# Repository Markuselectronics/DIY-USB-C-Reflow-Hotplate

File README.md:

# 🔥 DIY USB-C PD Reflow Hotplate

**A professional, pocket-sized soldering hotplate powered by USB-C Power Delivery.**

This repository contains all design files for the project.
👉 **Full Tutorial & Guide:** [Link to your Instructables Page]

## 📂 Repository Structure

* **`/Manufacturing`**: Gerber files for JLCPCB.
  * `HotPlate.zip` (Use SMT Assembly)
  * `Plate` (**Order as Aluminum PCB!**)
* **`/Firmware`**: Source code for the STM32 microcontroller.

## ⚠️ Warning
**Hot Surface!** This device reaches 250°C+. Use with caution.

## 🤝 Credits
Huge thanks to **JLCPCB** for sponsoring the PCBs for this project.

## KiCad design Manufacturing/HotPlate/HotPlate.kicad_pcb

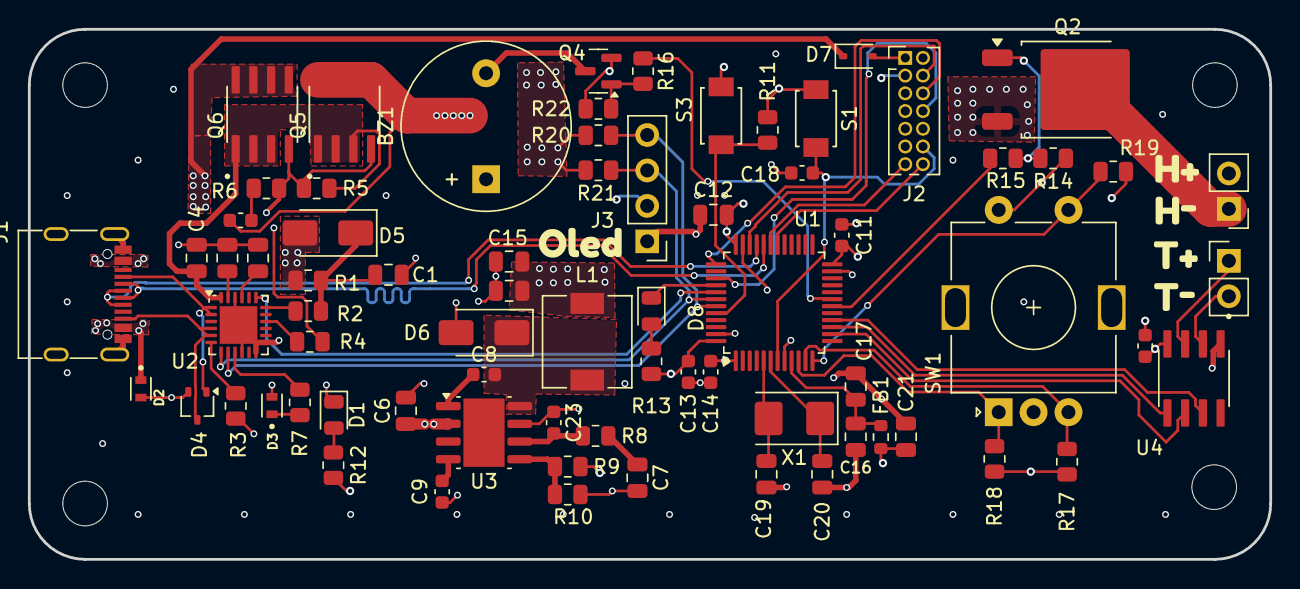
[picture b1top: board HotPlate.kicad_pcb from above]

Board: 4 copper layers, 89.0 x 38.0 mm, 82 parts (0 on the bottom side), 56 nets.

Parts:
BZ1: Buzzer; Buzzer_12x9.5RM7.6
C1, C2, C3, C4, C17, C21: 1uF; C_0805_2012Metric
C5, C8, C11, C13, C14, C18, C22: 100nF; C_0603_1608Metric
C6, C12: 10uF; C_0805_2012Metric
C7: 6n8; C_0805_2012Metric
C9: 8n2; C_0603_1608Metric
C10, C15: 47uF; C_0805_2012Metric
C16: 10nF; C_0805_2012Metric
C19, C20: 20pF; C_0805_2012Metric
C23: 10pF; C_0603_1608Metric
D1: green; D_0805_2012Metric
D2, D3: ESDA25P35-1U1M; TVS_ESDA25P35-1U1M
D4: ESDA25W; SOT-323_SC-70
D5, D6: SS14; D_SMA
D7: 1N5819WS; D_SOD-323
D8: yellow; D_0805_2012Metric
FB1: 120R; R_0603_1608Metric
H1, H2, H3, H4: MountingHole; MountingHole_3.2mm_M3
J1: USB-C; SHOU HAN TYPE-C 16PIN 2MD(073)
J2: Conn_ST_STDC14; PinHeader_2x07_P1.27mm_Vertical
J3: OLED-Display; PinHeader_1x04_P2.54mm_Vertical
J4: Thermocouple; PinHeader_1x02_P2.54mm_Vertical
J5: Heating Element; PinHeader_1x02_P2.54mm_Vertical
L1: 18uH; L_6.3x6.3_H3
Q2: MDD50N03D; TO-252-2
Q4: SS8050; SOT-23
Q5, Q6: AO4485; SOIC127P600X175-8N
R1: 470R; R_0805_2012Metric
R2: 1k; R_0805_2012Metric
R3, R9, R11, R14, R17, R18, R19, R22: 10k; R_0805_2012Metric
R4: 22k; R_0805_2012Metric
R5, R7: 100k; R_0805_2012Metric
R6: 100R; R_0805_2012Metric
R8: 4k99; R_0805_2012Metric
R10: 3k3; R_0805_2012Metric
R12, R13, R20, R21: 4k7; R_0805_2012Metric
R15: 270R; R_0805_2012Metric
R16: 3k9; R_0805_2012Metric
S1, S3: TS-1088-AR02016; SW_TS-1088-AR02016
SW1: RotaryEncoder; RotaryEncoder_Alps_EC11E-Switch_Vertical_H20mm
U1: STM32F103C8T6; LQFP-48_7x7mm_P0.5mm
U2: STUSB4500QTR; QFN-24-1EP_4x4mm_P0.5mm_EP2.7x2.7mm
U3: TPS54331DR; Texas_R-PDSO-G8_EP2.95x4.9mm_Mask2.4x3.1mm
U4: MAX6675ISA_; SOIC127P600X175-8N
X1: 8MHz; Crystal_SMD_5032-2Pin_5.0x3.2mm
kibuzzard-6914F22F: G***; kibuzzard-6914F22F
kibuzzard-6914F142: G***; kibuzzard-6914F142
kibuzzard-6914F203: G***; kibuzzard-6914F203
kibuzzard-6914F211: G***; kibuzzard-6914F211
kibuzzard-6914F240: G***; kibuzzard-6914F240

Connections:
+3.3V: BZ1.1 (+), C10.1, C11.1, C12.1, C13.1, C14.1, C15.1, C21.1, C22.1, FB1.2, J2.3 (VCC), J3.2, L1.2, R9.2, R12.1, R13.1, R17.2, R18.2, R19.2, R20.1, R21.2, S3.2, U1.1 (VBAT), U1.24 (VDD), U1.36 (VDD), U1.48 (VDD), U4.4 (VCC)
+3.3VA: C16.1, C17.1, FB1.1, U1.9 (VDDA)
/BOOT0: R11.1, S3.1, U1.44 (BOOT0)
/Buzzer: R16.1, U1.19 (PB1)
/CC1: D4.1 (K), J1.A5 (CC1), U2.1 (CC1DB), U2.2 (CC1)
/CC2: D4.3 (K), J1.B5 (CC2), U2.4 (CC2), U2.5 (CC2DB)
/D+: J1.A6 (D+), J1.B6 (D+), U1.33 (PA12)
/D-: J1.A7 (D-), J1.B7 (D-), U1.32 (PA11)
/Debug_SWCLK: J2.6 (JCLK/SWCLK), U1.37 (PA14)
/Debug_SWDIO: J2.4 (JTMS/SWDIO), U1.34 (PA13)
/Debug_SWO: J2.8 (JTDO/SWO), U1.39 (PB3)
/Debug_UART1_RX: J2.13 (VCP_RX), U1.31 (PA10)
/Debug_UART1_TX: J2.14 (VCP_TX), U1.30 (PA9)
/HSE_IN: C19.2, U1.5 (PD0), X1.2
/HSE_OUT: C20.2, U1.6 (PD1), X1.1
/HeatingElement: R15.1, U1.18 (PB0)
/I2C_SCL: J3.3, R21.1, U1.42 (PB6), U2.7 (SCL)
/I2C_SDA: J3.4, R20.2, U1.43 (PB7), U2.8 (SDA)
/NRST: C18.1, J2.12 (~RST), S1.1, U1.7 (NRST)
/PD_ALERT: U1.41 (PB5), U2.19 (ALERT)
/RESET: R3.2, U2.6 (RESET)
/RoEnc_A: R18.1, SW1.A, U1.10 (PA0)
/RoEnc_B: R17.1, SW1.B, U1.11 (PA1)
/RoEnc_Switch: R19.1, SW1.S1, U1.12 (PA2)
/SPI_CS_TH: U1.14 (PA4), U4.6 (~CS)
/SPI_MISO: U1.16 (PA6), U4.7 (SO)
/SPI_SCK: U1.15 (PA5), U4.5 (SCK)
/T+: J4.1, U4.3 (T+)
/T-: J4.2, U4.2 (T-)
/VBUS_EN_SNK: R4.1, U2.16 (VBUS_EN_SNK)
/VBUS_VS_DISCH: R2.1, U2.18 (VBUS_VS_DISCH)
/VDD: C4.2, Q5.1, Q5.2, Q5.3, Q6.1, Q6.2, Q6.3, R5.2, U2.24 (VDD)
/Vsense: R9.1, R10.2, U3.5 (VSENSE)
/Vsink: C5.1, J5.2, Q5.5, Q5.6, Q5.7, Q5.8
/Vsnk: D3.C, R7.2
/status_LED: D8.1 (K), U1.40 (PB4)
GND: C1.2, C2.1, C3.1, C4.1, C6.2, C7.2, C9.2, C10.2, C11.2, C12.2, C13.2, C14.2, C15.2, C16.2, C17.2, C18.2, C19.1, C20.1, C21.2, C22.2, C23.1, D1.1 (K), D2.A, D3.A, D4.2 (A), D6.2 (A), J1.A1 (GND), J1.A12 (GND), J1.B1 (GND), J1.B12 (GND), J1.S1 (SHIELD), J2.5 (GND), J2.7 (GND), J2.11 (GNDDetect), J3.1, Q2.3 (S), Q4.2 (E), R3.1, R10.1, R11.2, R14.1, R22.2, S1.2, SW1.C, SW1.S2, U1.8 (VSSA), U1.23 (VSS), U1.35 (VSS), U1.47 (VSS), U2.10 (GND), U2.12 (ADDR0), U2.13 (ADDR1), U2.22 (VSYS), U2.25 (GND), U3.7 (GND), U4.1 (GND)
unnamed: BZ1.2 (-), Q4.3 (C)
unnamed: C5.2, R6.2
unnamed: C7.1, R8.2
unnamed: D1.2 (A), R12.2
unnamed: C1.1, D5.1 (K), R1.1, R2.2
unnamed: C8.2, D6.1 (K), L1.1, U3.8 (PH)
unnamed: D7.2 (A), J2.1 (5V)
unnamed: D8.2 (A), R13.2
unnamed: J5.1, Q2.2 (D)
unnamed: Q2.1 (G), R14.2, R15.2
unnamed: Q4.1 (B), R16.2, R22.1
unnamed: Q5.4, Q6.4, R4.2, R5.1, R6.1
unnamed: R7.1, U2.9 (DISCH)
unnamed: C3.2, U2.21 (VREG_1V2)
unnamed: C2.2, U2.23 (VREG_2V7)
unnamed: C8.1, U3.1 (BOOT)
unnamed: C23.2, R8.1, U3.6 (COMP)
unnamed: C9.1, U3.4 (SS)
VBUS: C6.1, D2.C, D5.2 (A), D7.1 (K), J1.A4 (VBUS), J1.A9 (VBUS), J1.B4 (VBUS), J1.B9 (VBUS), Q6.5, Q6.6, Q6.7, Q6.8, R1.2, U3.2 (VIN)

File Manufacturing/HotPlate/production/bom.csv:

Designator,Footprint,Quantity,Value,LCSC Part #
BZ1,Buzzer_12x9.5RM7.6,1,Buzzer,C96093
"C1, C17, C2, C21, C3, C4",0805,6,1uF,C28323
"C10, C15",0805,2,47uF,C1745
"C11, C13, C14, C18, C22, C5, C8",0603,7,100nF,C1590
"C12, C6",0805,2,10uF,C15850
C16,0805,1,10nF,C1710
"C19, C20",0805,2,20pF,C1798
C23,0603,1,10pF,C1634
C7,0805,1,6n8,C1755
C9,0603,1,8n2,C1322360
D1,0805,1,green,C2297
"D2, D3",TVS_ESDA25P35-1U1M,2,ESDA25P35-1U1M,C1974707
D4,SOT-323_SC-70,1,ESDA25W,C2935152
"D5, D6",D_SMA,2,SS14,C2480
D7,D_SOD-323,1,1N5819WS,C191023
D8,0805,1,yellow,C2296
FB1,0603,1,120R,C14709
J1,SHOU HAN TYPE-C 16PIN 2MD(073),1,USB-C,C2765186
L1,L_6.3x6.3_H3,1,18uH,C168016
Q2,TO-252-2,1,MDD50N03D,
Q4,SOT-23,1,SS8050,C2150
"Q5, Q6",SOIC127P600X175-8N,2,AO4485,C51499
R1,0805,1,470R,C17710
R10,0805,1,3k3,C26010
"R11, R14, R17, R18, R19, R22, R3, R9",0805,8,10k,C17414
"R12, R13, R20, R21",0805,4,4k7,C17673
R15,0805,1,270R,C17590
R16,0805,1,3k9,C17614
R2,0805,1,1k,C17513
R4,0805,1,22k,C17560
"R5, R7",0805,2,100k,C149504
R6,0805,1,100R,C17408
R8,0805,1,4k99,C17677
"S1, S3",SW_TS-1088-AR02016,2,TS-1088-AR02016,C720477
SW1,RotaryEncoder_Alps_EC11E-Switch_Vertical_H20mm,1,RotaryEncoder,C370970
U1,LQFP-48_7x7mm_P0.5mm,1,STM32F103C8T6,C8734
U2,QFN-24-1EP_4x4mm_P0.5mm_EP2.7x2.7mm,1,STUSB4500QTR,C2678061
U3,Texas_R-PDSO-G8_EP2.95x4.9mm_Mask2.4x3.1mm,1,TPS54331DR,C9865
U4,SOIC127P600X175-8N,1,MAX6675ISA_,C16030
X1,Crystal_SMD_5032-2Pin_5.0x3.2mm,1,8MHz,C115962

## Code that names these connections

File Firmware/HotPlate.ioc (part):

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Mcu.Name=STM32F103C(8-B)Tx
Mcu.Package=LQFP48
Mcu.UserName=STM32F103C8Tx
PA0-WKUP.Signal=S_TIM2_CH1_ETR
PA1.Signal=S_TIM2_CH2
PA13.Mode=Serial_Wire
PA13.Signal=SYS_JTMS-SWDIO
PA14.Mode=Serial_Wire
PA14.Signal=SYS_JTCK-SWCLK
PA2.GPIOParameters=GPIO_Label
PA2.GPIO_Label=button_notPressed
PA2.Signal=GPIO_Input
PA4.GPIOParameters=GPIO_Label
PA4.GPIO_Label=SPI1_CS_TH
PA4.Signal=GPIO_Output
PA5.Mode=RX_Only_Simplex_Unidirect_Master
PA5.Signal=SPI1_SCK
PA6.Mode=RX_Only_Simplex_Unidirect_Master
PA6.Signal=SPI1_MISO
PB0.GPIOParameters=GPIO_Label
PB0.GPIO_Label=HeatingPlate_on
PB0.Signal=GPIO_Output
PB1.GPIOParameters=GPIO_Label
PB1.GPIO_Label=Buzzer_beep
PB1.Signal=S_TIM3_CH4
PB4.GPIOParameters=PinState,GPIO_PuPd,GPIO_Label
PB4.GPIO_Label=status_LED_activeLow
PB4.GPIO_PuPd=GPIO_NOPULL
PB4.PinState=GPIO_PIN_SET
PB4.Signal=GPIO_Output
PB6.Mode=I2C
PB6.Signal=I2C1_SCL
PB7.Mode=I2C
PB7.Signal=I2C1_SDA
PD0-OSC_IN.Mode=HSE-External-Oscillator
PD0-OSC_IN.Signal=RCC_OSC_IN
PD1-OSC_OUT.Mode=HSE-External-Oscillator
PD1-OSC_OUT.Signal=RCC_OSC_OUT
RCC.SYSCLKFreq_VALUE=48000000
RCC.SYSCLKSource=RCC_SYSCLKSOURCE_PLLCLK
board=custom

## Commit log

2026-01-21 main
2026-02-05 Remove 3D Print section from README
    Removed 3D Print section from README.
2026-02-05 Create Firmware
2026-02-05 Create test
2026-02-05 Create rt
2026-02-05 Update HotPlate
